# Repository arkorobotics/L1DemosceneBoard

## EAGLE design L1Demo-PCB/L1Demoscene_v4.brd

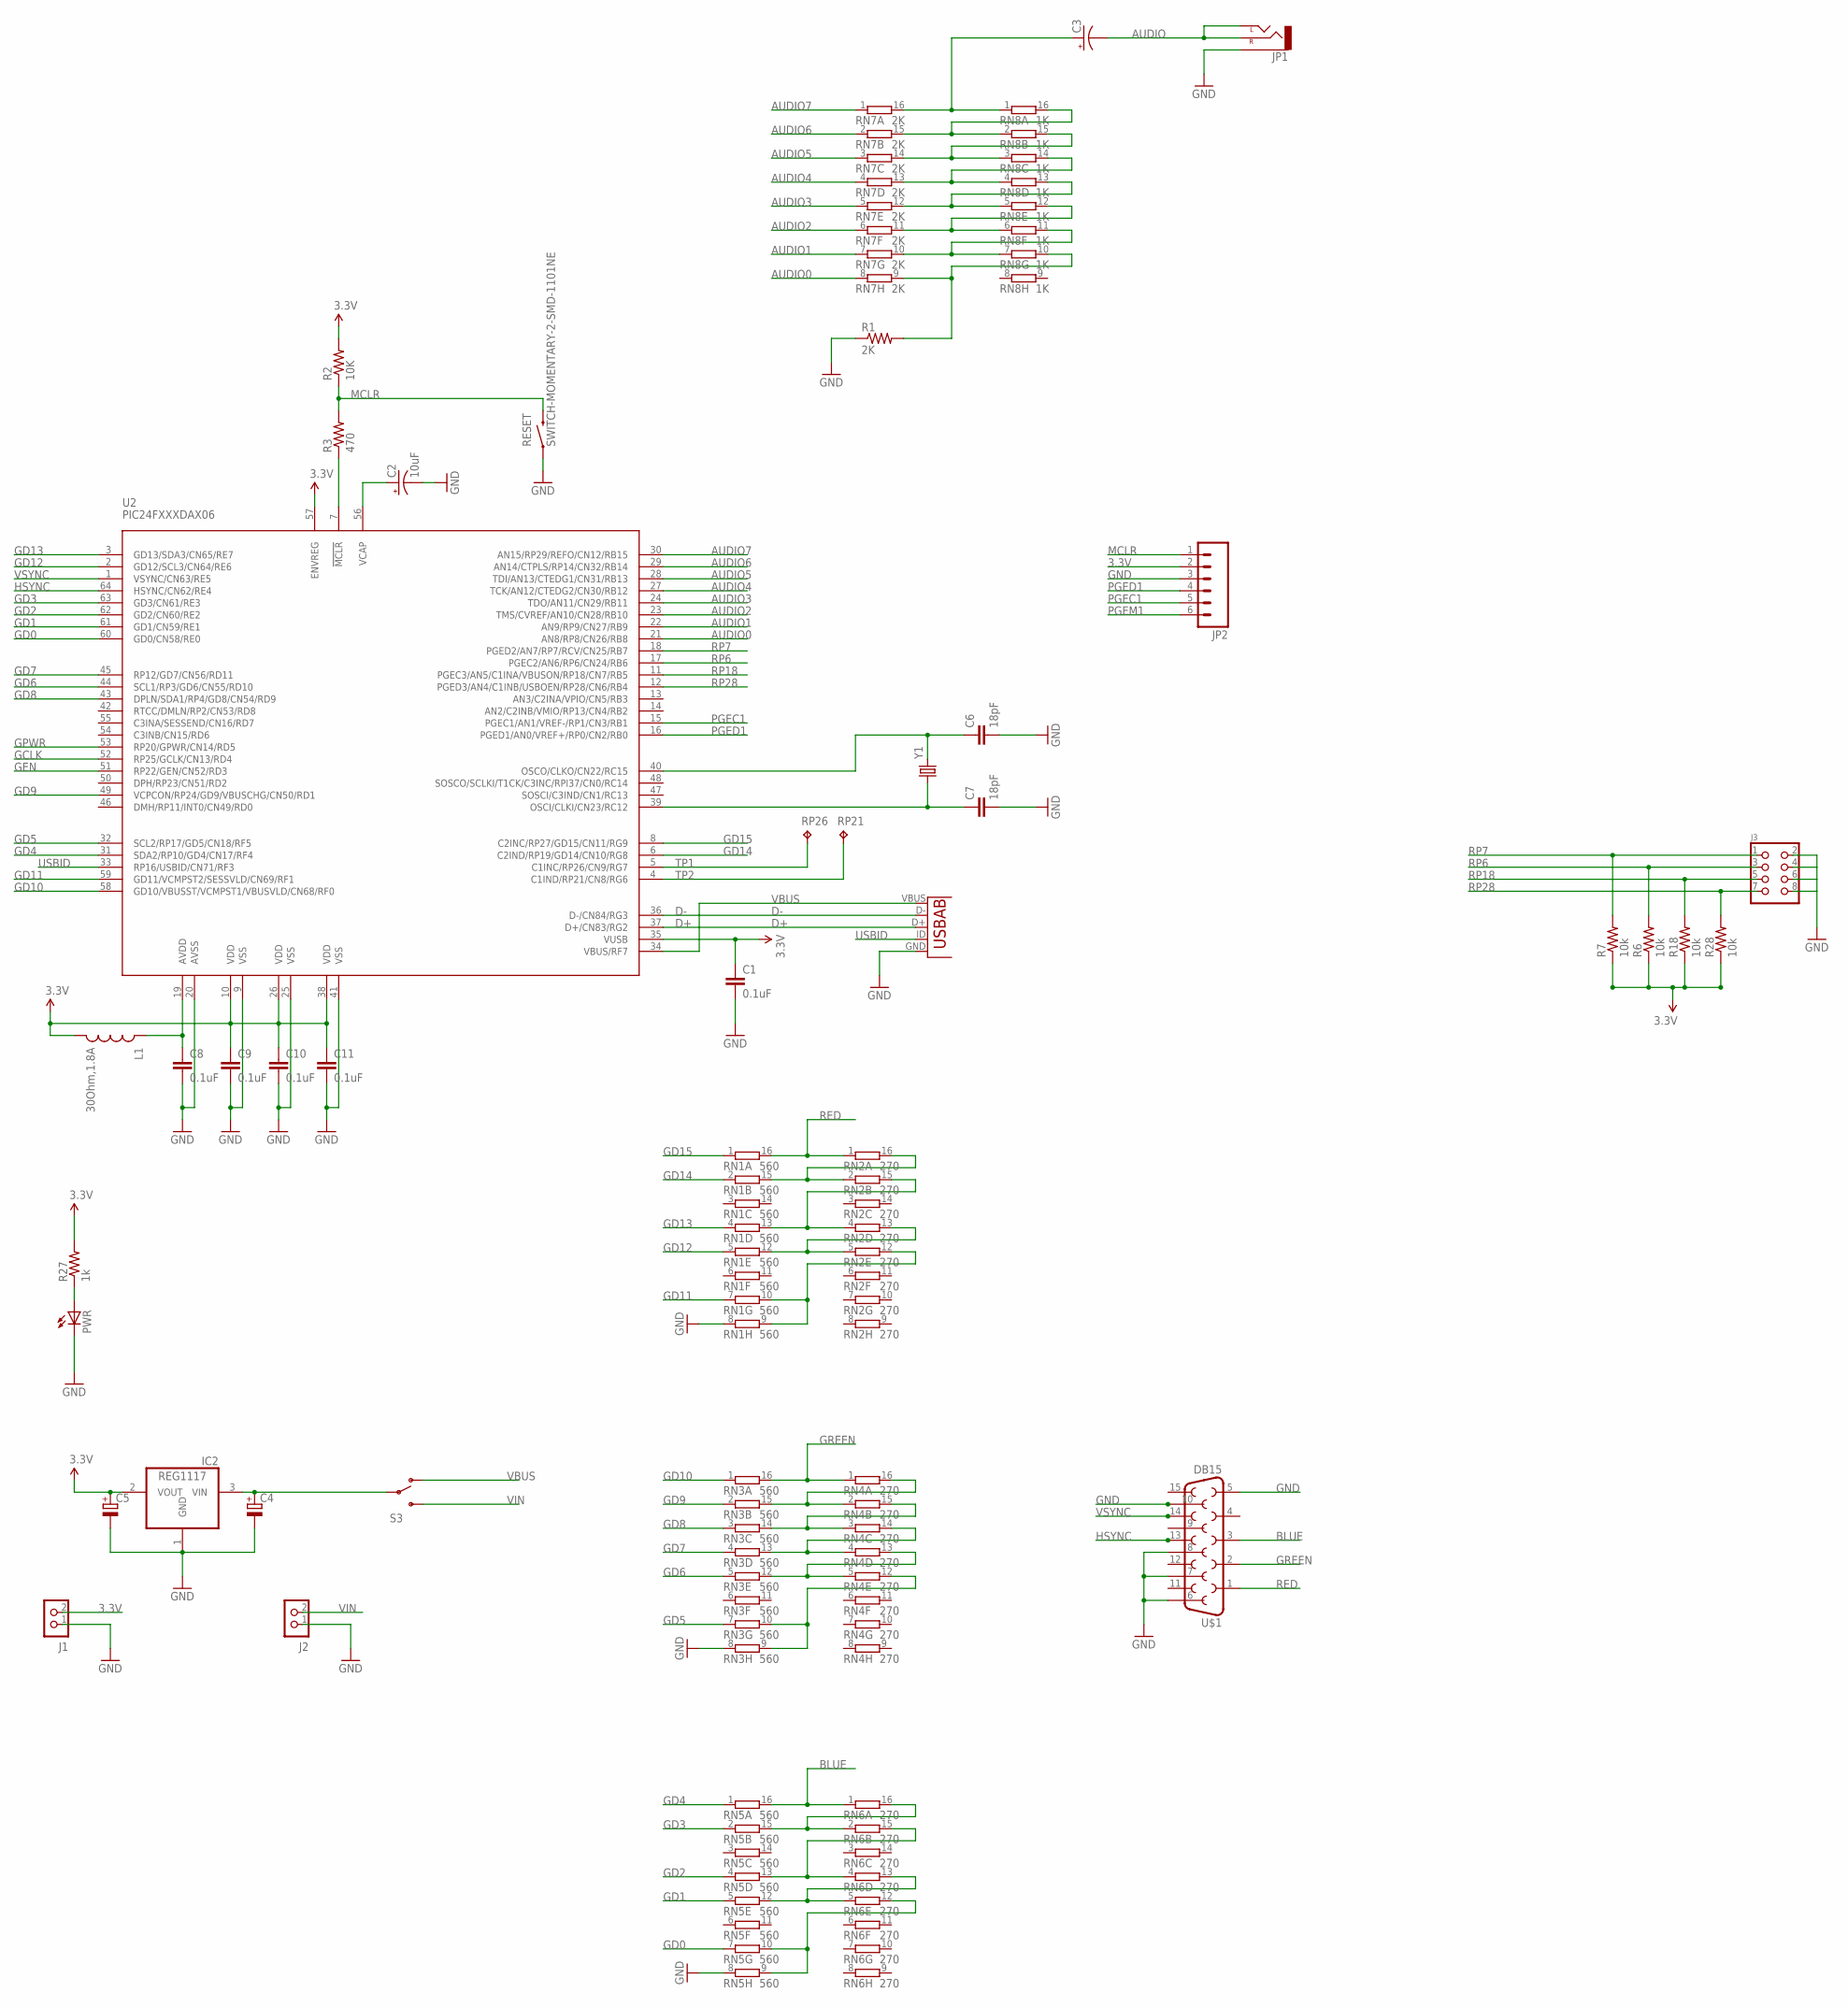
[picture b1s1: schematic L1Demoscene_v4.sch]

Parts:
C1, C8, C9, C10, C11: 0.1uF; 0603-CAP
C2: 10uF; EIA3216
C3: CAP_POL1206; EIA3216
C4, C5: CAPACITOR_POL-SMC_A; SMC_A
C6, C7: 18pF; 0603-CAP
IC2: REG1117; SOT223
J1, J2: CON_HEADER_1X02-PTH; M1X2
J3: CON_HEADER_2X04-PTH; M2X4
JP1: AUDIO-JACKPTH; AUDIO-JACK
JP2: M06SIP; 1X06
L1: 30Ohm,1.8A; 0603
PWR: LED-0603; LED-603
R1: 2K; 0603-RES
R2: 10K; 0603-RES
R3: 470; 0603-RES
R6, R7, R18, R28: 10k; 0603-RES
R27: 1k; 0603-RES
RESET: SWITCH-MOMENTARY-2-SMD-1101NE; TACTILE-SWITCH-1101NE
RN1, RN3, RN5: 560; EXB2HV
RN2, RN4, RN6: 270; EXB2HV
RN7: 2K; EXB2HV
RN8: 1K; EXB2HV
RP21, RP26: TPTP06R; TP06R
S3: SWITCH-SPDT-SMD-A; SWITCH-SPST-SMD-A
U2: PIC24FXXXDAX06; PIC24FXXX_TQFP64
U3: USB-AB; USB-AB-MICRO-SMD
U$1: DB15
Y1: CRYSTAL5X3; CRYSTAL-SMD-5X3

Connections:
3.3V: C1.1, C5.+, C9.1, C10.1, C11.1, IC2.2 (VOUT), J1.2, JP2.2, L1.2, R2.2, R6.1, R7.1, R18.1, R27.2, R28.1, U2.10 (VDD), U2.26 (VDD), U2.35 (VUSB), U2.38 (VDD), U2.57 (ENVREG)
AUDIO: C3.C (-), JP1.RING (RIGHT), JP1.TIP (LEFT)
AUDIO0: RN7.8 (1), U2.21 (AN8/RP8/CN26/RB8)
AUDIO1: RN7.7 (1), U2.22 (AN9/RP9/CN27/RB9)
AUDIO2: RN7.6 (1), U2.23 (TMS/CVREF/AN10/CN28/RB10)
AUDIO3: RN7.5 (1), U2.24 (TDO/AN11/CN29/RB11)
AUDIO4: RN7.4 (1), U2.27 (TCK/AN12/CTEDG2/CN30/RB12)
AUDIO5: RN7.3 (1), U2.28 (TDI/AN13/CTEDG1/CN31/RB13)
AUDIO6: RN7.2 (1), U2.29 (AN14/CTPLS/RP14/CN32/RB14)
AUDIO7: RN7.1, U2.30 (AN15/RP29/REFO/CN12/RB15)
BLUE: RN5.16 (2), RN6.1, U$1.3
D+: U2.37 (D+/CN83/RG2), U3.D+
D-: U2.36 (D-/CN84/RG3), U3.D-
GCLK: U2.52 (RP25/GCLK/CN13/RD4)
GD0: RN5.7 (1), U2.60 (GD0/CN58/RE0)
GD1: RN5.5 (1), U2.61 (GD1/CN59/RE1)
GD2: RN5.4 (1), U2.62 (GD2/CN60/RE2)
GD3: RN5.2 (1), U2.63 (GD3/CN61/RE3)
GD4: RN5.1, U2.31 (SDA2/RP10/GD4/CN17/RF4)
GD5: RN3.7 (1), U2.32 (SCL2/RP17/GD5/CN18/RF5)
GD6: RN3.5 (1), U2.44 (SCL1/RP3/GD6/CN55/RD10)
GD7: RN3.4 (1), U2.45 (RP12/GD7/CN56/RD11)
GD8: RN3.3 (1), U2.43 (DPLN/SDA1/RP4/GD8/CN54/RD9)
GD9: RN3.2 (1), U2.49 (VCPCON/RP24/GD9/VBUSCHG/CN50/RD1)
GD10: RN3.1, U2.58 (GD10/VBUSST/VCMPST1/VBUSVLD/CN68/RF0)
GD11: RN1.7 (1), U2.59 (GD11/VCMPST2/SESSVLD/CN69/RF1)
GD12: RN1.5 (1), U2.2 (GD12/SCL3/CN64/RE6)
GD13: RN1.4 (1), U2.3 (GD13/SDA3/CN65/RE7)
GD14: RN1.2 (1), U2.6 (C2IND/RP19/GD14/CN10/RG8)
GD15: RN1.1, U2.8 (C2INC/RP27/GD15/CN11/RG9)
GEN: U2.51 (RP22/GEN/CN52/RD3)
GND: C1.2, C2.C (-), C4.-, C5.-, C6.2, C7.2, C8.2, C9.2, C10.2, C11.2, IC2.1 (GND), J1.1, J2.1, J3.2, J3.4, J3.6, J3.8, JP1.SLEEVE, JP2.3, PWR.C, R1.1, RESET.P$1 (1), RN1.8 (1), RN3.8 (1), RN5.8 (1), U2.9 (VSS), U2.20 (AVSS), U2.25 (VSS), U2.41 (VSS), U3.GND, U$1.5, U$1.6, U$1.7, U$1.8, U$1.10
GPWR: U2.53 (RP20/GPWR/CN14/RD5)
GREEN: RN3.16 (2), RN4.1, U$1.2
HSYNC: U2.64 (HSYNC/CN62/RE4), U$1.13
MCLR: JP2.1, R2.1, R3.2, RESET.P$2 (2)
unnamed: C8.1, L1.1, U2.19 (AVDD)
unnamed: C3.A (+), RN7.16 (2), RN8.1
unnamed: C7.1, U2.39 (OSCI/CLKI/CN23/RC12), Y1.1
unnamed: R3.1, U2.7 (!MCLR)
unnamed: RN7.15 (2), RN8.2 (1), RN8.16 (2)
unnamed: RN7.14 (2), RN8.3 (1), RN8.15 (2)
unnamed: C4.+, IC2.3 (VIN), S3.2
unnamed: C2.A (+), U2.56 (VCAP)
unnamed: RN7.13 (2), RN8.4 (1), RN8.14 (2)
unnamed: PWR.A, R27.1
unnamed: RN7.12 (2), RN8.5 (1), RN8.13 (2)
unnamed: RN7.11 (2), RN8.6 (1), RN8.12 (2)
unnamed: RN7.10 (2), RN8.7 (1), RN8.11 (2)
unnamed: RN3.15 (2), RN4.2 (1), RN4.16 (2)
unnamed: RN3.14 (2), RN4.3 (1), RN4.15 (2)
unnamed: RN3.13 (2), RN4.4 (1), RN4.14 (2)
unnamed: RN3.12 (2), RN4.5 (1), RN4.13 (2)
unnamed: RN3.9 (2), RN3.10 (2), RN4.12 (2)
unnamed: R1.2, RN7.9 (2), RN8.10 (2)
unnamed: C6.1, U2.40 (OSCO/CLKO/CN22/RC15), Y1.3 (2)
unnamed: RN1.13 (2), RN2.4 (1), RN2.15 (2)
unnamed: RN1.15 (2), RN2.2 (1), RN2.16 (2)
unnamed: RN1.12 (2), RN2.5 (1), RN2.13 (2)
unnamed: RN1.9 (2), RN1.10 (2), RN2.12 (2)
unnamed: RN5.15 (2), RN6.2 (1), RN6.16 (2)
unnamed: RN5.13 (2), RN6.4 (1), RN6.15 (2)
unnamed: RN5.12 (2), RN6.5 (1), RN6.13 (2)
unnamed: RN5.9 (2), RN5.10 (2), RN6.12 (2)
PGEC1: JP2.5, U2.15 (PGEC1/AN1/VREF-/RP1/CN3/RB1)
PGED1: JP2.4, U2.16 (PGED1/AN0/VREF+/RP0/CN2/RB0)
PGEM1: JP2.6
RED: RN1.16 (2), RN2.1, U$1.1
RP6: J3.3, R6.2, U2.17 (PGEC2/AN6/RP6/CN24/RB6)
RP7: J3.1, R7.2, U2.18 (PGED2/AN7/RP7/RCV/CN25/RB7)
RP18: J3.5, R18.2, U2.11 (PGEC3/AN5/C1INA/VBUSON/RP18/CN7/RB5)
RP28: J3.7, R28.2, U2.12 (PGED3/AN4/C1INB/USBOEN/RP28/CN6/RB4)
TP1: RP26.TP, U2.5 (C1INC/RP26/CN9/RG7)
TP2: RP21.TP, U2.4 (C1IND/RP21/CN8/RG6)
USBID: U2.33 (RP16/USBID/CN71/RF3), U3.ID (USBID)
VBUS: S3.1 (O), U2.34 (VBUS/RF7), U3.VBUS
VIN: J2.2, S3.3 (S)
VSYNC: U2.1 (VSYNC/CN63/RE5), U$1.14

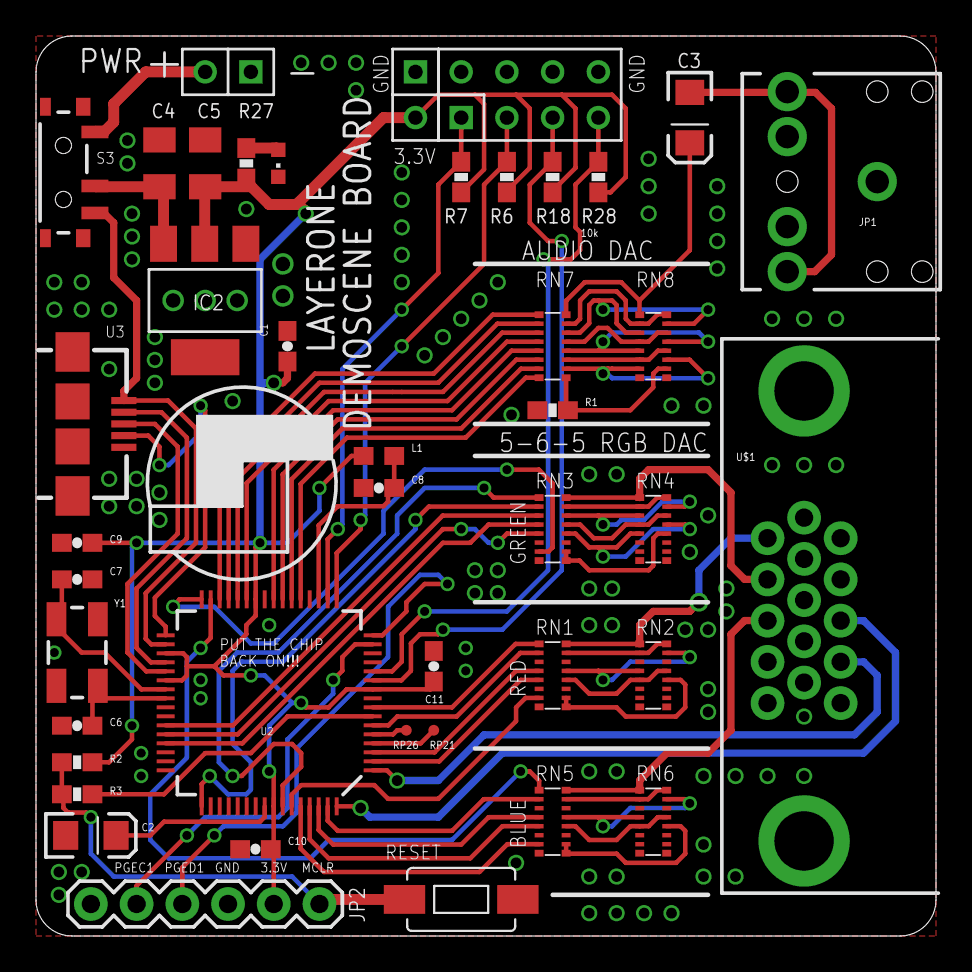
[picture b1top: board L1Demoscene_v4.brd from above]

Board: 2 copper layers, 50.0 x 50.0 mm, 44 parts (0 on the bottom side), 74 nets.

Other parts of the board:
U$2: STM32-PROX_L1LOGO

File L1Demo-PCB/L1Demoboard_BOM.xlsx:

Part | Value | Device | Package | Description | Link | QTY | 100 Boards | 50 Boards
C1,C8,C9,C10,C11 | 0.1uF | CAP0603-CAP | 0603-CAP | Capacitor | http://www.digikey.com/product-detail/en/GRM188R71C104KA01D/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 | 5 | 3 | 1.76
C2,C3,C4,C5 | 10uF | CAP_POL1206 | EIA3216 | Capacitor | http://www.digikey.com/product-detail/en/T491A106K010AT/399-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 | 4 | 53.872 | 33.68 | EXPENSIVE
C6,C7 | 18pF | CAP0603-CAP | 0603-CAP | Capacitor | http://www.digikey.com/product-detail/en/GRM1885C1H180JA01D/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 | 2 | 3.82 | 1.91
IC2 | REG1117 | REG1117 | SOT223 | 800mA | http://www.digikey.com/product-detail/en/LM1117MPX-3.3%2FNOP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 | 1 | 115.16 | 65.8 | EXPENSIVE
J2 | CON_HEADER_1X02-PTH | CON_HEADER_1X02-PTH | M1X2 |  | http://www.digikey.com/product-detail/en/67997-210HLF/609-32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 | 1 | 10.4 | 5.6
J3 | CON_HEADER_2X04-PTH | CON_HEADER_2X04-PTH | M2X5 |  | http://www.digikey.com/product-detail/en/67997-210HLF/609-32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 | 1 | 35.4 | 18.47
JP1 | AUDIO-JACKPTH | AUDIO-JACK | 3.5mm | Audio | http://www.digikey.com/product-detail/en/SJ1-3525N/CP1-3525N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 | 1 | 0 | 0 | EXPENSIVE
JP2 | M06SIP | 1X06 | Header | 6 | http://www.digikey.com/product-detail/en/961106-5604-AR/3M94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 | 1 | 32.200000000000003 | 16.8
L1 | 30Ohm,1.8A | INDUCTOR0402 | C0402 | Inductors | http://www.digikey.com/product-detail/en/ELJ-PF2N7DFB/PCD189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 | 1 | 13.06 | 6.99
PWR | LED-0603 | LED-603 | Light | Emitting | http://www.digikey.com/product-detail/en/LTST-C191KRKT/160-1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 | 1 | 12.96 | 11.9
R1 | 2K | RESISTOR0603-RES | 0603-RES | Resistor | http://www.digikey.com/scripts/DkSearch/dksus.dll?Detail&ite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 | 1 | 1.1399999999999999 | 0.75
R2,R6,R7,R18,R28 | 10K | RESISTOR0603-RES | 0603-RES | Resistor | http://www.digikey.com/product-detail/en/RC0603JR-0710KL/311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 | 5 | 0.45 | 0.4
R3 | 470 | RESISTOR0603-RES | 0603-RES | Resistor | http://www.digikey.com/product-detail/en/RC0603JR-07470RL/31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 | 1 | 0.45 | 0.4
R27 | 1k | RESISTOR0603-RES | 0603-RES | Resistor | http://www.digikey.com/product-detail/en/RC0603FR-071KL/311-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 | 1 | 0.6 | 0.54
RN1,RN3,RN5 | 560 | 8R-NEXB2HV | EXB2HV | DIL | http://www.digikey.com/product-detail/en/EXB-2HV561JV/Y1561C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 | 3 | 39.372 | 25.32
RN2,RN4,RN6 | 270 | 8R-NEXB2HV | EXB2HV | DIL | http://www.digikey.com/product-detail/en/EXB-2HV271JV/Y1271C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 | 3 | 39.369999999999997 | 25.32
RN7 | 2K | 8R-NEXB2HV | EXB2HV | DIL | http://www.digikey.com/product-detail/en/EXB-2HV222JV/Y1222C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 | 1 | 16.88 | 10.94
RN8 | 1K | 8R-NEXB2HV | EXB2HV | DIL | http://www.digikey.com/scripts/DkSearch/dksus.dll?Detail&ite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 | 1 | 16.88 | 10.94
S3 | SWITCH-SPDT-SMD-A | SWITCH-SPST-SMD-A | SPDT | Switch | http://www.digikey.com/scripts/DkSearch/dksus.dll?Detail&ite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 | 1 | 62.26 | 32.69
U$1 | DB15 | DB15 | DB15 | DB15 | http://www.digikey.com/product-detail/en/1734344-1/A35119-ND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 | 1 | 0 | 0
U2 | PIC24FJ256DA206 | PIC24FXXXDAX06 | PIC24FXXX_TQFP64 | PIC24FXXXDAX06 | http://www.mouser.com/Search/ProductDetail.aspx?R=PIC24FJ256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 | 1 | 584 | 322.5 | EXPENSIVE
U3 | USB-AB | USB-AB-MICRO-SMD | This | is | http://www.digikey.com/product-detail/en/10104111-0001LF/609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 | 1 | 56.87 | 29.67
Y1 | CRYSTAL5X3 | CRYSTAL-SMD-5X3 | Various | standard | http://www.digikey.com/product-search/en?KeyWords=535-9720-1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 | 1 | 76 | 42.94
 | Push Switch |  |  |  | http://www.digikey.com/product-detail/en/RS-282G05A3-SM%20RT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 | 1 | 55 | 30.25 | EXPENSIVE
 |  |  |  |  |  |  | Total part cost of 100 Boards | Total part cost of 50 Boards
 |  |  |  |  |  |  | 1229.1439999999998 | 695.56999999999994
 |  |  |  |  |  |  | Part cost per board | Part cost per board
 |  |  |  |  |  |  | 12.291439999999998 | 13.911399999999999
 |  |  |  |  |  |  | PNP total cost | PNP total cost
 |  |  |  |  |  |  | 900 | 525
 |  |  |  |  |  |  | PNP cost per board | PNP cost per board
 |  |  |  |  |  |  | 6.5 | 10.5
 |  |  |  |  |  |  | PCB cost | PCB cost
 |  |  |  |  |  |  | 198 | 70
 |  |  |  |  |  |  | Total cost to manufacture 100 | Total cost to manufacture 50
 |  |  |  |  |  |  | 2327.1439999999998 | 1290.57
 |  |  |  |  |  |  | Total cost per board | Total cost per board
 |  |  |  |  |  |  | 23.271439999999998 | 25.811399999999999

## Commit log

2014-12-28 :circus_tent: Added .gitattributes & .gitignore files
2014-12-28 Added Leo's ASM example code
    Added Leo's ASM example code, default code.
2015-01-01 Added audio demos
    Added audio demos
2015-01-01 Added L1 Demoscene Board PCB
    Added L1 Demoscene Board PCB
2015-01-01 Color bar test
    color bar test, framebuffer still in the works, this is not complete,
    but compiles.
2015-01-11 Added bldewolf l1demo example
    bldewolf wrote an example c program https://github.com/bldewolf/l1demo
2015-01-13 uncommented config bits
    uncommented config bits
2015-02-14 L1 Demoscene Board Example with flames and music
    Written by Datagram and Hotdogs, this demo displays sprites, draws
    animated squares and plays a simple song.
2015-02-15 fixed display issue
    fixed display issue
2015-02-15 removed exe
    removed exe
2017-06-25 Added panelized PCBs and production BOM
    Added panelized PCBs and production BOM

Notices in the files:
parts and their libraries:
SparkFun-Capacitors: Licensing: CC v3.0 Share-Alike You are welcome to use this library for commercial purposes.
